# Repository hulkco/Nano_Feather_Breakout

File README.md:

#**The Shield**

**This breakout puts the Arduino Nano Family into a Feather Form Factor**

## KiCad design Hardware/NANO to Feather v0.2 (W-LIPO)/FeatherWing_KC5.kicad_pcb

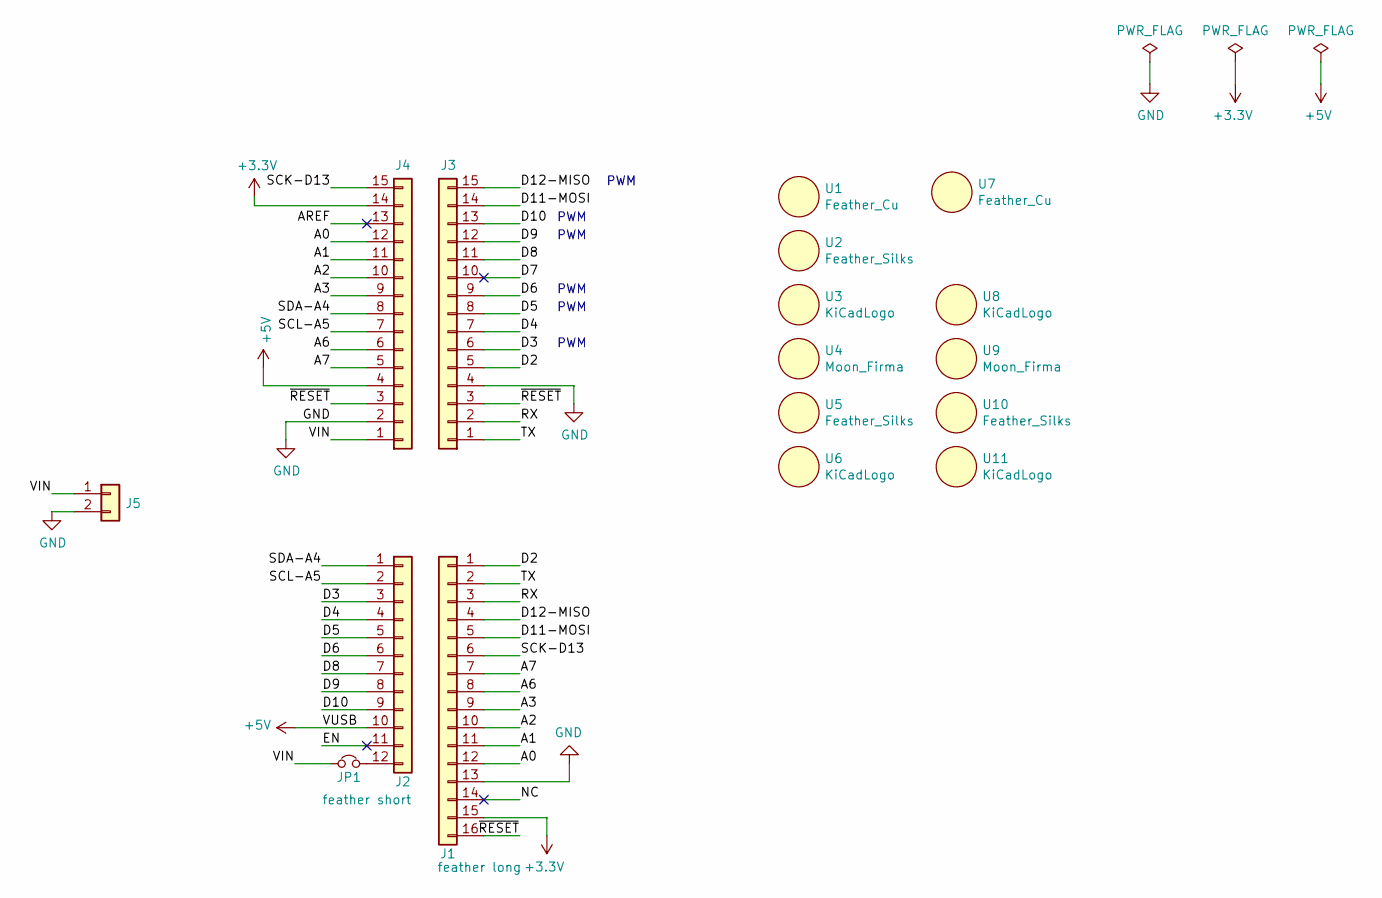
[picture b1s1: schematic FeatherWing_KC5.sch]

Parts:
J1: feather long; PinHeader_1x16_P2.54mm_Vertical
J2: feather short; PinHeader_1x12_P2.54mm_Vertical
J3, J4: Conn_01x15; PinSocket_1x15_P2.54mm_Vertical
J5: Conn_01x02; JST-PH_S2B-PH-SM4-TB
JP1: Jumper_NC_Small; SolderJumper-2_P1.3mm_Bridged_RoundedPad1.0x1.5mm
U1, U7: Feather_Cu; Feather_CU
U2: Feather_Silks
U3, U8: KiCadLogo; Ki-2500
U4, U9: Moon_Firma; Moon_Firma_SilkS
U5, U10: Feather_Silks; Moon_The_Shield_SilkS
U6, U11: KiCadLogo; OSHW-Logo2_7.3x6mm_SilkScreen

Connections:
+3V3: J1.15, J4.14
+5V: J2.10, J4.4
/A0: J1.12, J4.12
/A1: J1.11, J4.11
/A2: J1.10, J4.10
/A3: J1.9, J4.9
/A6: J1.8, J4.6
/A7: J1.7, J4.5
/AREF: J4.13
/D2: J1.1, J3.5
/D3: J2.3, J3.6
/D4: J2.4, J3.7
/D5: J2.5, J3.8
/D6: J2.6, J3.9
/D7: J3.10
/D8: J2.7, J3.11
/D9: J2.8, J3.12
/D10: J2.9, J3.13
/D11-MOSI: J1.5, J3.14
/D12-MISO: J1.4, J3.15
/EN: J2.11
/NC: J1.14
/RX: J1.3, J3.2
/SCK-D13: J1.6, J4.15
/SCL-A5: J2.2, J4.7
/SDA-A4: J2.1, J4.8
/TX: J1.2, J3.1
/VIN: J4.1, J5.1, JP1.1
/~RESET: J1.16, J3.3, J4.3
GND: J1.13, J3.4, J4.2, J5.2
unnamed: J2.12, JP1.2

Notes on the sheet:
PWM

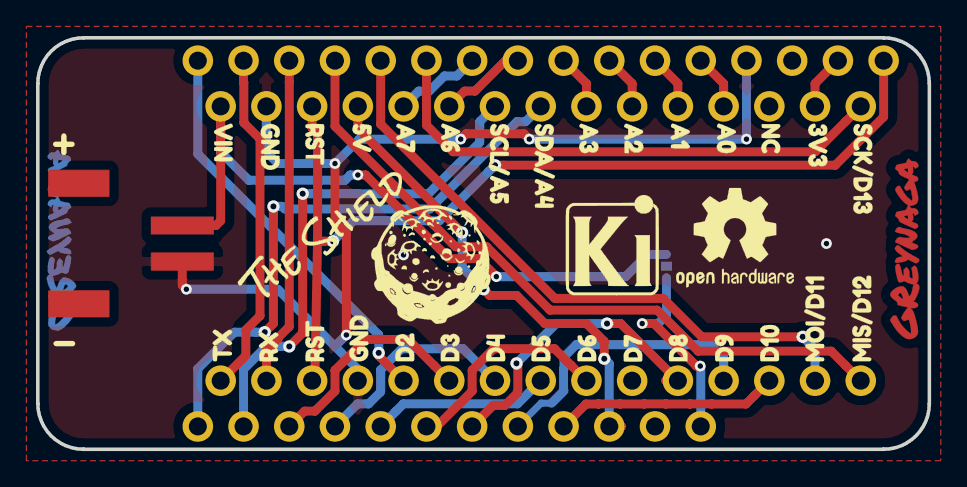
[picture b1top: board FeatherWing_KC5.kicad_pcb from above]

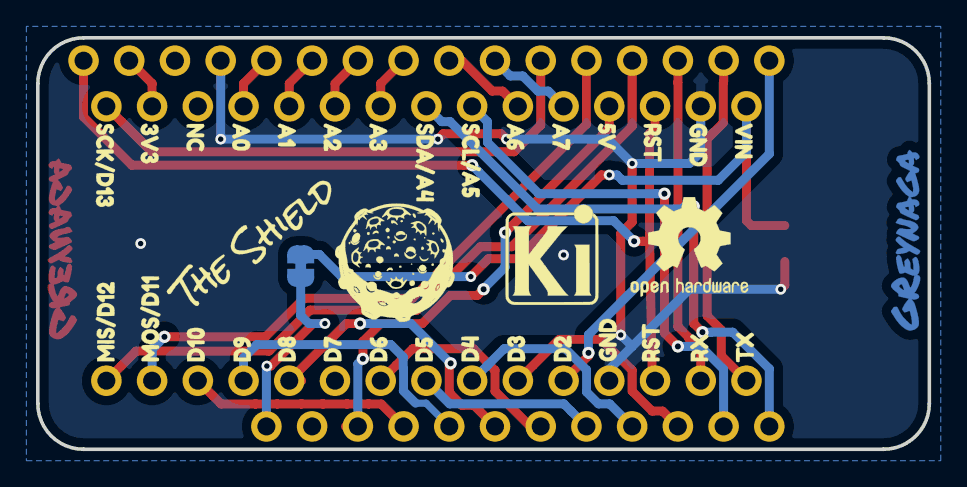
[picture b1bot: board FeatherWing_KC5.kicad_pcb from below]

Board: 2 copper layers, 49.5 x 22.9 mm, 17 parts (8 on the bottom side), 27 nets.

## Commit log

2020-02-08 First upload
2020-02-09 Add v0.2 w-lipo
2021-04-08 minosr changes
2021-04-08 Add gitignore definitions
2021-04-08 update gitignore definition
2021-04-08 Update gitignore
